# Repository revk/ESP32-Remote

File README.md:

# ESP32-Remote

Now at [Codeberg](https://codeberg.org/RevK/ESP32-Remote)

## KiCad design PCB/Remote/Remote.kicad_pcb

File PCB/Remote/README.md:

# Remote

## Trademark

This project is subject to the licence in the LICENCE file, and even if that says it is an open source project, you cannot sell boards or cases bearing the Andrews & Arnold Ltd name, the A&A logo, the registered trademark AJK logo or other registered trademarks, or any GS1 allocated EANs/barcode assigned to Andrews & Arnold Ltd.

## PCB Designs

These files are for use with [KiCAD](https://www.kicad.org).

- [Remote](Remote.kicad_pro)

## 3D

3D case designs are normally automatically created from the PCB so as to ensure correct details and placement of apertures, etc.

- [blankplate](blankplate.stl)
- [Knob](Knob.stl)
- [Remote------](Remote------.stl)
- [Remote-----B](Remote-----B.stl)
- [Remote----I-](Remote----I-.stl)
- [Remote----IB](Remote----IB.stl)
- [Remote---C--](Remote---C--.stl)
- [Remote---C-B](Remote---C-B.stl)
- [Remote---CI-](Remote---CI-.stl)
- [Remote---CIB](Remote---CIB.stl)
- [Remote--D---](Remote--D---.stl)
- [Remote--D--B](Remote--D--B.stl)
- [Remote--D-I-](Remote--D-I-.stl)
- [Remote--D-IB](Remote--D-IB.stl)
- [Remote--DC--](Remote--DC--.stl)
- [Remote--DC-B](Remote--DC-B.stl)
- [Remote--DCI-](Remote--DCI-.stl)
- [Remote--DCIB](Remote--DCIB.stl)
- [Remote-Base](Remote-Base.stl)
- [Remote-P----](Remote-P----.stl)
- [Remote-P---B](Remote-P---B.stl)
- [Remote-P--I-](Remote-P--I-.stl)
- [Remote-P--IB](Remote-P--IB.stl)
- [Remote-P-C--](Remote-P-C--.stl)
- [Remote-P-C-B](Remote-P-C-B.stl)
- [Remote-P-CI-](Remote-P-CI-.stl)
- [Remote-P-CIB](Remote-P-CIB.stl)
- [Remote-PD---](Remote-PD---.stl)
- [Remote-PD--B](Remote-PD--B.stl)
- [Remote-PD-I-](Remote-PD-I-.stl)
- [Remote-PD-IB](Remote-PD-IB.stl)
- [Remote-PDC--](Remote-PDC--.stl)
- [Remote-PDC-B](Remote-PDC-B.stl)
- [Remote-PDCI-](Remote-PDCI-.stl)
- [Remote-PDCIB](Remote-PDCIB.stl)

## PCB Images

---

*Auto generated README.md 2026-01-03T10:27:57*

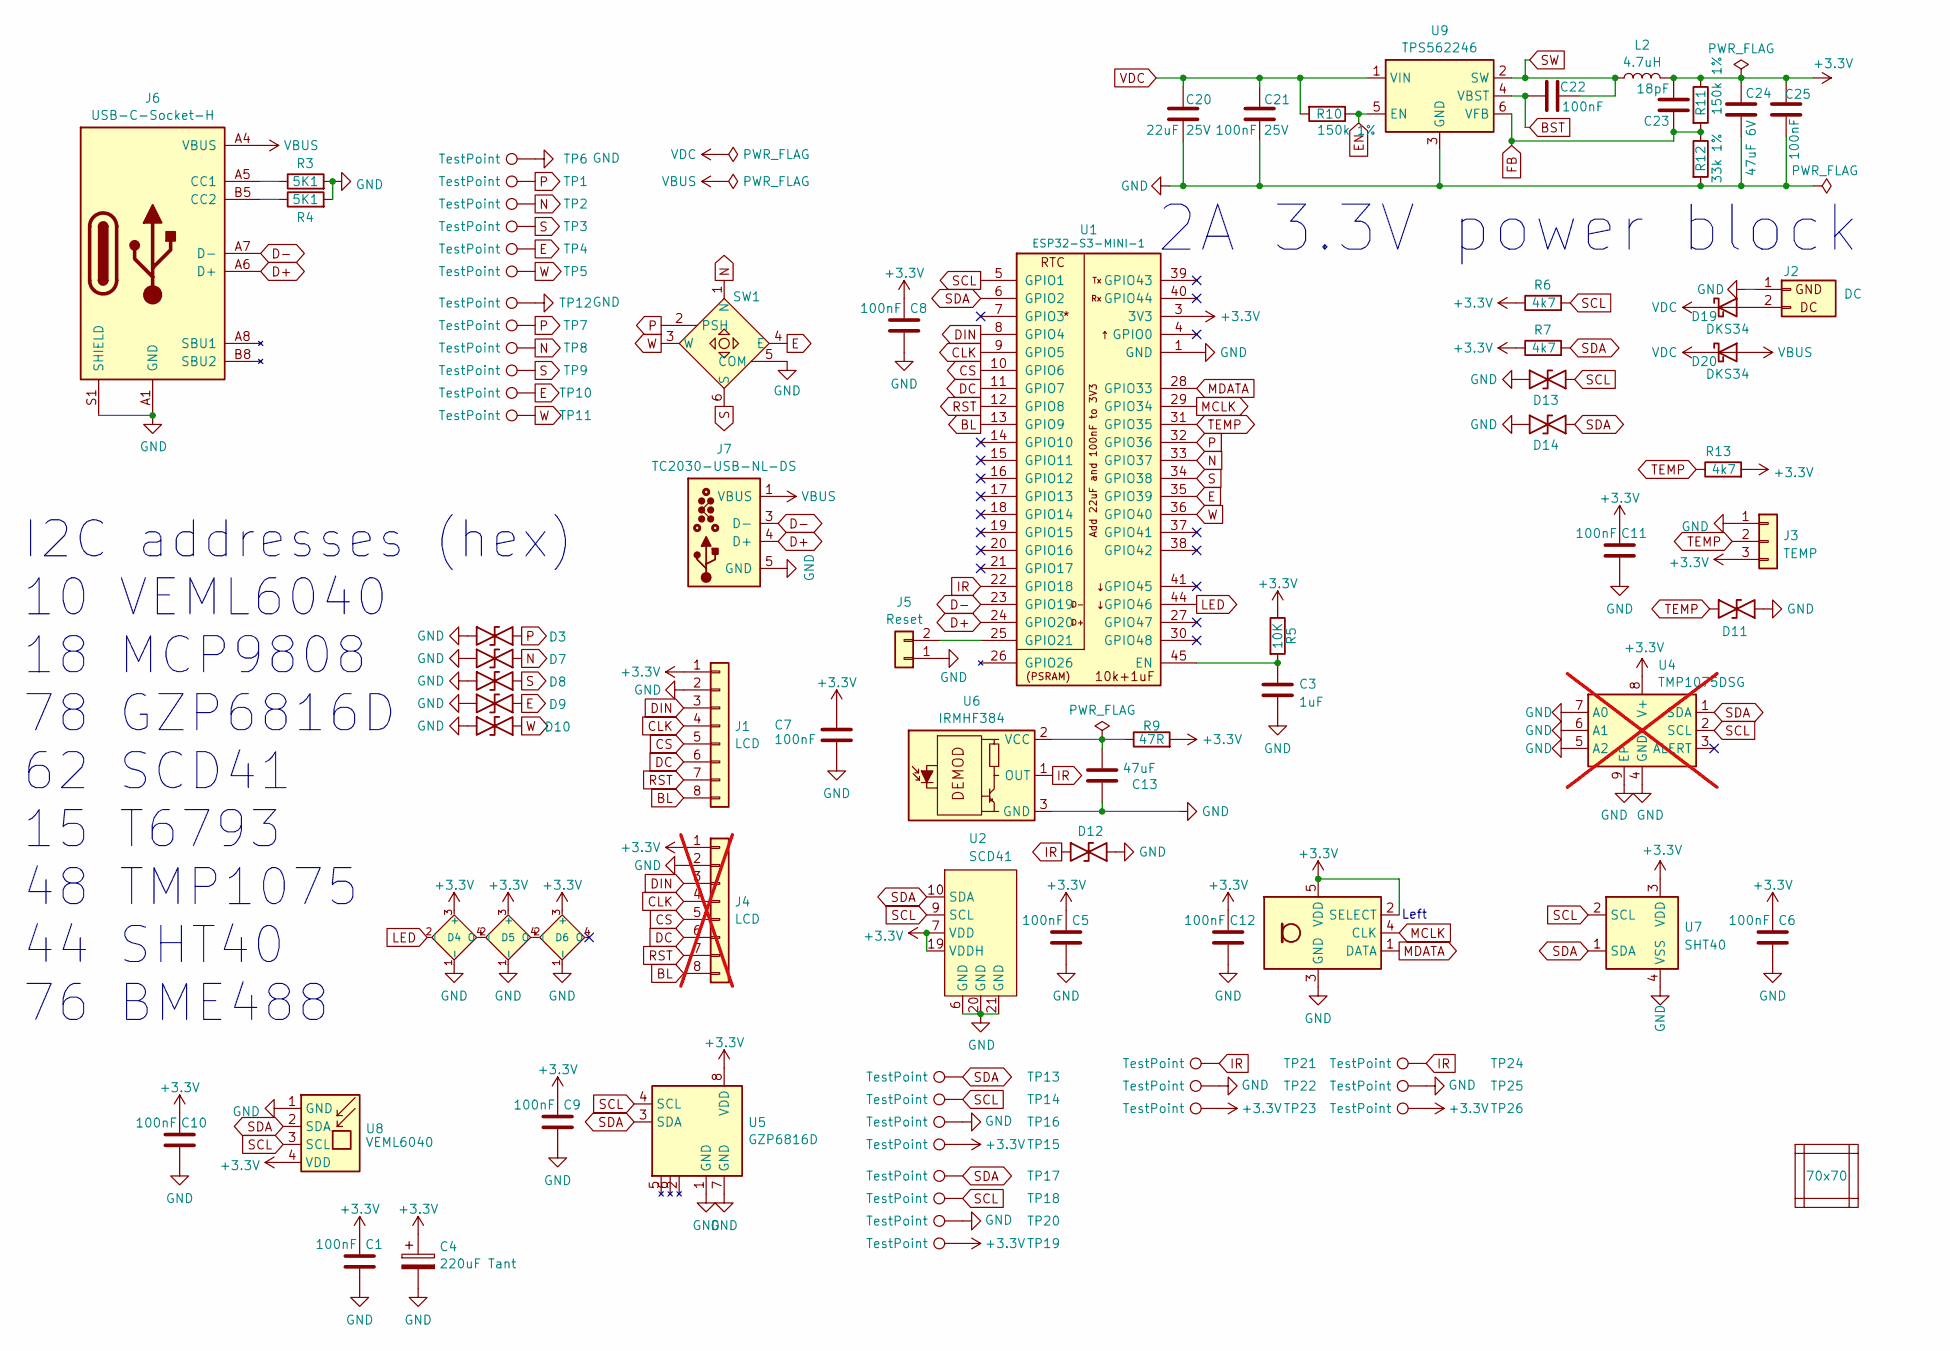
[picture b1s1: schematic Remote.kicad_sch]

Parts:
C1, C5, C6, C8, C9, C10, C11, C12, C22, C25: 100nF; C_0201; MPN C76934
C3: 1uF; C_0201
C4: 220uF Tant; CP_EIA-3528-21_Kemet-B; MPN C122649
C7: 100nF; C_0201
C13: 47uF; C_0603
C20: 22uF 25V; C_0805; MPN C45783
C21: 100nF 25V; C_0402; MPN C56392
C23: 18pF; C_0201; MPN C62164
C24: 47uF 6V; C_0805; MPN C16780
D3, D7, D8, D9, D10, D11, D12, D13, D14: DFN1006-2L; MPN C5137770
D4: XL-1615RGBC-2812B; SMD1615-Side; MPN C5349954
D5, D6: XL-1010RGBC-WS2812B; SMD1615-Side; MPN C5349954
D19, D20: DKS34; D_SOD-123FL; MPN C727076
J1: LCD; LCD2; MPN C42380985
J2: DC; WAGO-2060-452-998-404; MPN C2765055
J3: TEMP; WAGO-2060-453-998-404; MPN C2765056
J4: LCD; PinHeader_1x08_P2.54mm_Vertical; MPN C42380985; not fitted
J5: Reset; AA-Pad
J6: USB-C-Socket-H; MPN C709357
J7: TC2030-USB-NL-DS; Tag-Connect_TC2030-IDC-NL_2x03_P1.27mm_Vertical
L2: 4.7uH; L_5x5; MPN C307876
PCB1: 70x70; PCB7070
R3, R4: 5K1; R_0201; MPN C473460
R5: 10K; R_0201; MPN C102690
R6, R7, R13: 4k7; R_0201; MPN C7467262
R9: 47R; R_0402; MPN C854484
R10, R11: 150k 1%; R_0201; MPN C310173
R12: 33k 1%; R_0201; MPN C320835
SW1: Switch-Nav5; MPN C145900
T1: T3902_MEMS_Mic; T3902_MEMS_Mic_Open; MPN C3171752
TP1, TP2, TP3, TP4, TP5, TP7, TP8, TP9, TP10, TP11, TP13, TP14, TP15, TP17, TP18, TP19, TP21, TP23, TP24, TP26: TestPoint; TestPad
TP6, TP12, TP16, TP20, TP22, TP25: TestPoint; TestPadSquare
U1: ESP32-S3-MINI-1; MPN C3013941
U2: SCD41; MPN C3659294
U4: TMP1075DSG; WSON-8-1EP_2x2mm_P0.5mm_EP0.9x1.6mm_ThermalVias-Side; MPN C2870250; not fitted
U5: GZP6816D; Bosch_LGA-8_2x2.5mm_P0.65mm_ClockwisePinNumbering; MPN C3038127
U6: IRMHF384; IR-SMD-4P,3.35x3.9mm; MPN C7280961
U7: SHT40; Sensirion_DFN-4_1.5x1.5mm_P0.5mm_SHT4x-Side; MPN C2909890
U8: VEML6040; VEML6040-Side; MPN C78465
U9: TPS562246; SOT-5x3-6; MPN C41833479
V1, V2, V3, V4: VCUT70

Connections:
+3.3V: C1.2, C4.1, C5.2, C6.2, C7.1, C8.2, C9.2, C10.2, C11.2, C12.2, C23.2, C24.1, C25.2, D4.3 (+), D5.3 (+), D6.3 (+), J1.1, J3.3, J4.1, L2.2, R5.1, R6.1, R7.1, R9.2, R11.1, R13.2, T1.2 (SELECT), T1.5 (VDD), TP15.1, TP19.1, TP23.1, TP26.1, U1.3 (3V3), U2.7 (VDD), U2.19 (VDDH), U5.8 (VDD), U7.3 (VDD), U8.4 (VDD)
BL: J1.8, J4.8, U1.13 (GPIO9)
BST: C22.1, U9.4 (VBST)
CLK: J1.4, J4.4, U1.9 (GPIO5)
CS: J1.5, J4.5, U1.10 (GPIO6)
D+: J6.A6 (D+), J6.B6 (D+), J7.4 (D+), U1.24 (GPIO20)
D-: J6.A7 (D-), J6.B7 (D-), J7.2 (NC), J7.3 (D-), J7.6 (NC), U1.23 (GPIO19)
DC: J1.6, J4.6, U1.11 (GPIO7)
DIN: J1.3, J4.3, U1.8 (GPIO4)
E: D9.1, SW1.4 (E), TP4.1, TP10.1, U1.35 (GPIO39)
EN: R10.1, U9.5 (EN)
FB: C23.1, R11.2, R12.1, U9.6 (VFB)
GND: C1.1, C3.2, C4.2, C5.1, C6.1, C7.2, C8.1, C9.1, C10.1, C11.1, C12.1, C13.2, C20.2, C21.2, C24.2, C25.1, D3.2, D4.1 (-), D5.1 (-), D6.1 (-), D7.2, D8.2, D9.2, D10.2, D11.1, D12.1, D13.1, D14.1, J1.2, J2.1 (GND), J3.1, J4.2, J5.1, J6.A1 (GND), J6.A12 (GND), J6.B1 (GND), J6.B12 (GND), J6.S1 (SHIELD), J7.5 (GND), R3.2, R4.2, R12.2, SW1.5 (COM), T1.3 (GND), TP6.1, TP12.1, TP16.1, TP20.1, TP22.1, TP25.1, U1.1 (GND), U1.2 (GND), U1.42 (GND), U1.43 (GND), U1.46 (GND), U1.47 (GND), U1.48 (GND), U1.49 (GND), U1.50 (GND), U1.51 (GND), U1.52 (GND), U1.53 (GND), U1.54 (GND), U1.55 (GND), U1.56 (GND), U1.57 (GND), U1.58 (GND), U1.59 (GND), U1.60 (GND), U1.61 (GND), U1.62 (GND), U1.63 (GND), U1.64 (GND), U1.65 (GND), U2.6 (GND), U2.20 (GND), U2.21 (GND), U5.1 (GND), U5.7 (GND), U6.3 (GND), U6.4 (GND), U7.4 (VSS), U8.1 (GND), U9.3 (GND)
IR: D12.2, TP21.1, TP24.1, U1.22 (GPIO18), U6.1 (OUT)
LED: D4.2 (I), U1.44 (GPIO46)
MCLK: T1.4 (CLK), U1.29 (GPIO34)
MDATA: T1.1 (DATA), U1.28 (GPIO33)
N: D7.1, SW1.1 (N), TP2.1, TP8.1, U1.33 (GPIO37)
unnamed: D4.4 (O), D5.2 (I)
unnamed: D5.4 (O), D6.2 (I)
unnamed: D19.2 (A), J2.2 (DC)
unnamed: J5.2, U1.25 (GPIO21)
unnamed: J6.A5 (CC1), R3.1
unnamed: J6.B5 (CC2), R4.1
unnamed: C3.1, R5.2, U1.45 (EN)
unnamed: C13.1, R9.1, U6.2 (VCC)
P: D3.1, SW1.2 (PSH), TP1.1, TP7.1, U1.32 (GPIO36)
RST: J1.7, J4.7, U1.12 (GPIO8)
S: D8.1, SW1.6 (S), TP3.1, TP9.1, U1.34 (GPIO38)
SCL: D13.2, R6.2, TP14.1, TP18.1, U1.5 (GPIO1), U2.5 (DNC), U2.9 (SCL), U4.2 (SCL), U5.4 (SCL), U7.2 (SCL), U8.3 (SCL)
SDA: D14.2, R7.2, TP13.1, TP17.1, U1.6 (GPIO2), U2.10 (SDA), U5.3 (SDA), U7.1 (SDA), U8.2 (SDA)
SW: C22.2, L2.1, U9.2 (SW)
TEMP: D11.2, J3.2, R13.1, U1.31 (GPIO35)
VBUS: D20.2 (A), J6.A4 (VBUS), J6.A9 (VBUS), J6.B4 (VBUS), J6.B9 (VBUS), J7.1 (VBUS)
VDC: C20.1, C21.1, D19.1 (K), D20.1 (K), R10.2, U9.1 (VIN)
W: D10.1, SW1.3 (W), TP5.1, TP11.1, U1.36 (GPIO40)

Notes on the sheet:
2A 3.3V power block
I2C addresses (hex) 10 VEML6040 18 MCP9808 78 GZP6816D 62 SCD41 15 T6793 48 TMP1075 44 SHT40 76 BME488
Left

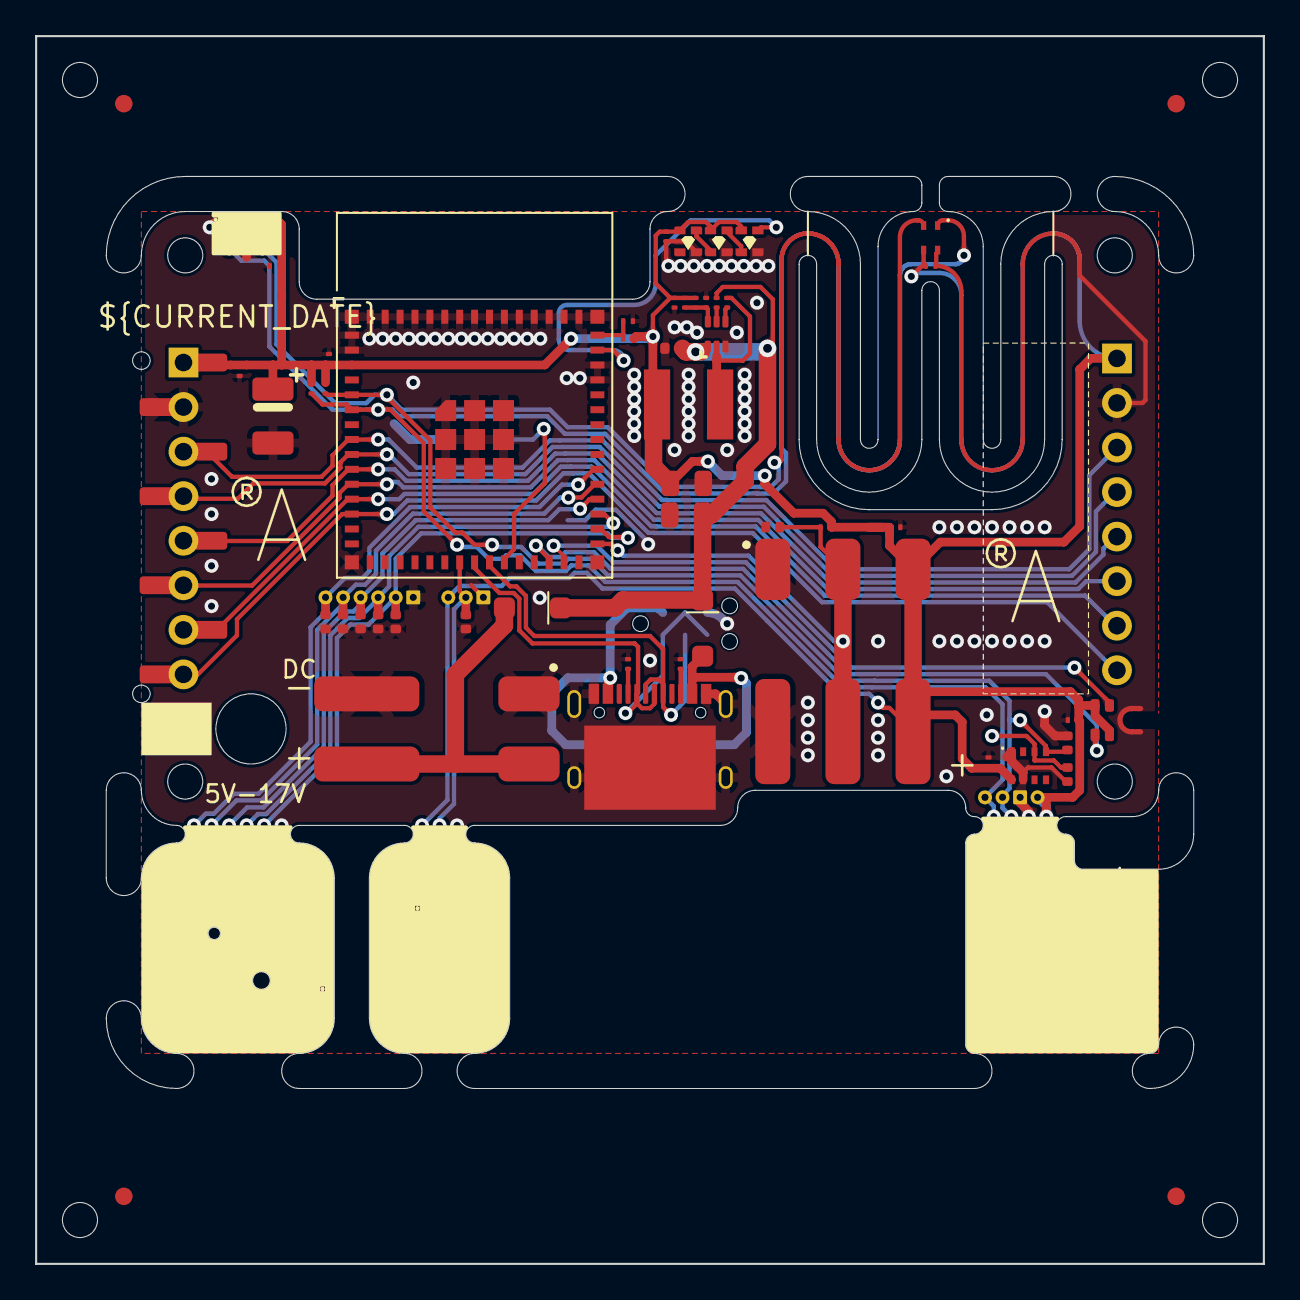
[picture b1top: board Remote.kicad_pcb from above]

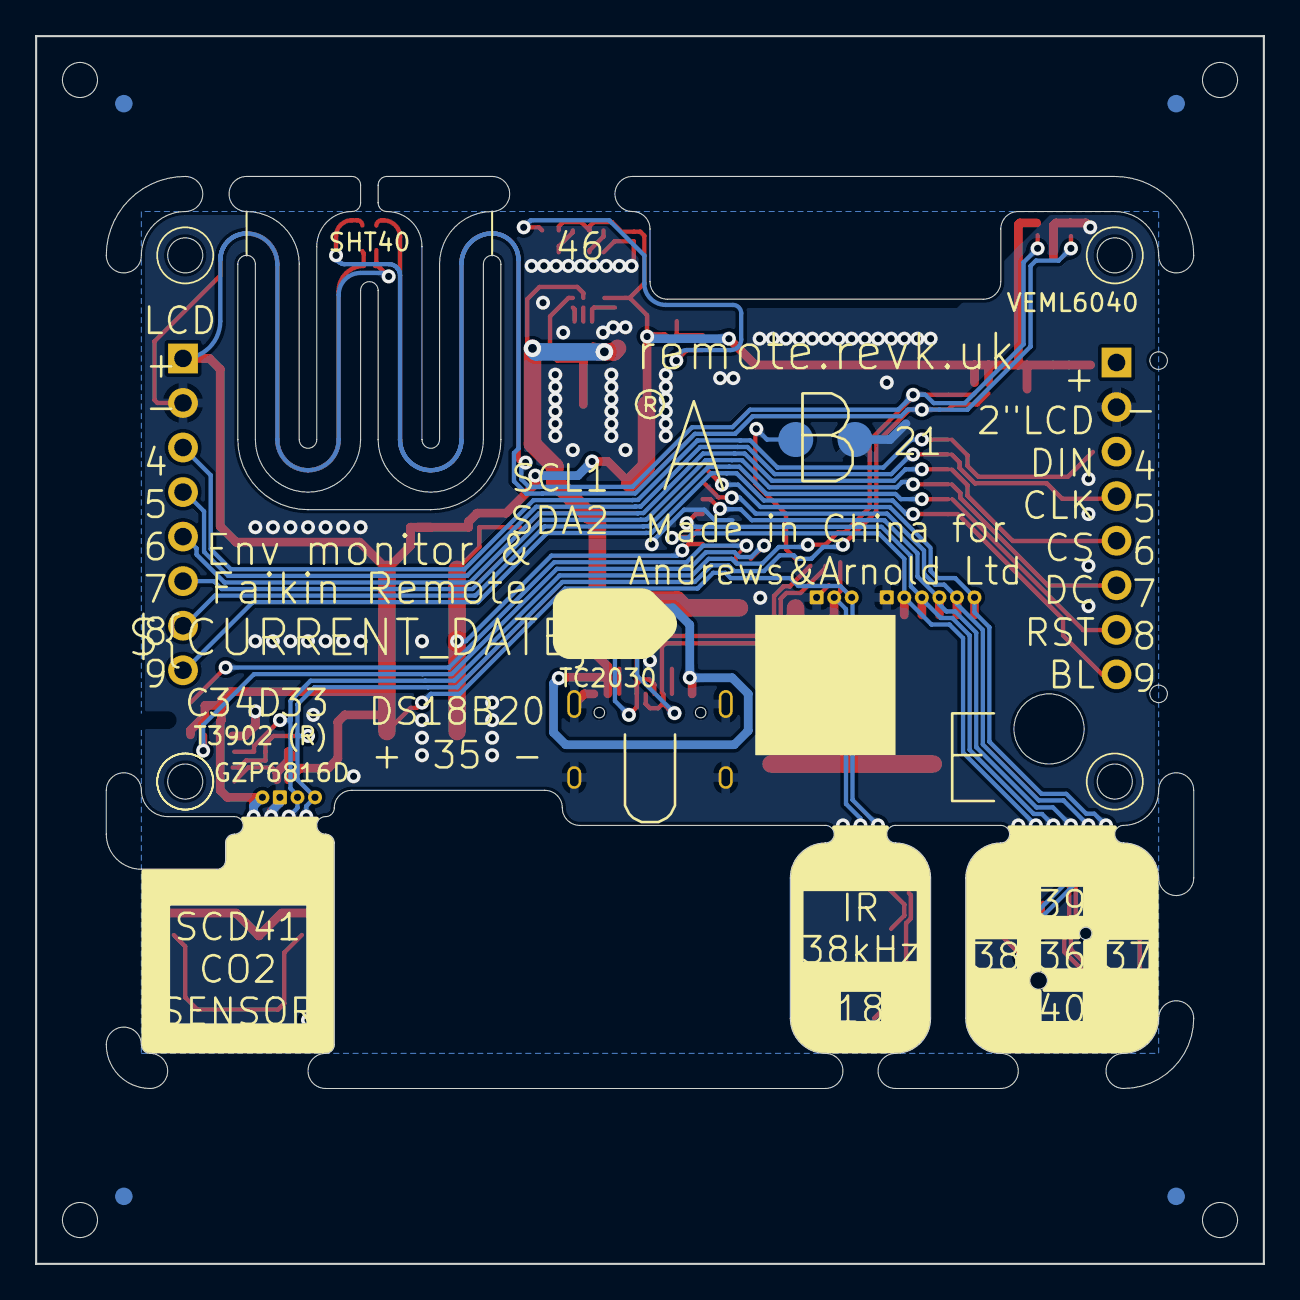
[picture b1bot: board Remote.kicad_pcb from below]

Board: 2 copper layers, 70.0 x 70.0 mm, 90 parts (3 on the bottom side), 36 nets.

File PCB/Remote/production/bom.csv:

Designator,Footprint,Quantity,Value,LCSC Part #
"C1, C10, C11, C12, C22, C25, C5, C6, C8, C9",C_0201,10,100nF,C76934
C13,C_0603,1,47uF,
C20,C_0805,1,22uF 25V,C45783
C21,C_0402,1,100nF 25V,C56392
C23,C_0201,1,18pF,C62164
C24,C_0805,1,47uF 6V,C16780
C3,C_0201,1,1uF,
C4,CP_EIA-3528-21_Kemet-B,1,220uF Tant,C122649
C7,C_0201,1,100nF,
"D10, D11, D12, D13, D14, D3, D7, D8, D9",DFN1006-2L,9,~,C5137770
"D19, D20",D_SOD-123FL,2,DKS34,C727076
D4,SMD1615-Side,1,XL-1615RGBC-2812B,C5349954
"D5, D6",SMD1615-Side,2,XL-1010RGBC-WS2812B,C5349954
J1,LCD2,1,LCD,C42380985
J2,WAGO-2060-452-998-404,1,DC,C2765055
J3,WAGO-2060-453-998-404,1,TEMP,C2765056
J6,USB-C-Socket-H,1,USB-C-Socket-H,C709357
L2,L_5x5,1,4.7uH,C307876
"R10, R11",R_0201,2,150k 1%,C310173
R12,R_0201,1,33k 1%,C320835
"R13, R6, R7",R_0201,3,4k7,C7467262
"R3, R4",R_0201,2,5K1,C473460
R5,R_0201,1,10K,C102690
R9,R_0402,1,47R,C854484
SW1,Switch-Nav5,1,~,C145900
T1,T3902_MEMS_Mic_Open,1,T3902_MEMS_Mic,C3171752
U1,ESP32-S3-MINI-1,1,ESP32-S3-MINI-1,C3013941
U2,SCD41,1,SCD41,C3659294
U5,Bosch_LGA-8_2x2.5mm_P0.65mm_ClockwisePinNumbering,1,GZP6816D,C3038127
U6,"IR-SMD-4P,3.35x3.9mm",1,IRMHF384,C7280961
U7,Sensirion_DFN-4_1.5x1.5mm_P0.5mm_SHT4x-Side,1,SHT40,C2909890
U8,VEML6040-Side,1,VEML6040,C78465
U9,SOT-5x3-6,1,TPS562246,C41833479

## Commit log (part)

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2025-05-05 tweak
2025-05-05 Tidy icons for Rh and CO2
2025-05-05 Beta
2025-05-05 Consistent spacing
2025-05-05 FFS again
2025-05-05 Release
2025-05-06 New btn and temp reporting
2025-05-06 New button working mode
2025-05-06 New button logic - 4 way not 5
2025-05-06 Library update
2025-05-06 Tidy
2025-05-06 D'Oh
2025-05-06 RH 2 places
2025-05-06 RH BLE fix
2025-05-07 Avoid radiator fighting cooling
2025-05-07 scd41to
2025-05-07 RH delay too
2025-05-08 Many tweaks including SCD41 temp offset
2025-05-08 Auocal
2025-05-08 Timed darkness
2025-05-08 autocal
2025-05-08 Reporting
2025-05-08 /status
2025-05-08 Rework
2025-05-08 Updated design
2025-05-09 Started on new casework
2025-05-10 Change to SHT so humidity when no CO2
2025-05-10 Cases
2025-05-10 Adjust radiator logic
2025-05-10 atest renders
2025-05-10 case
2025-05-10 rad on until close
2025-05-10 0 rh fix
2025-05-10 Tweak rad
2025-05-10 Latest render
2025-05-10 Tidy no mode
2025-05-10 TGweak
2025-05-11 Radiator control logic taken from old envmon code.
2025-05-11 Rad timer fix
2025-05-11 Help
2025-05-11 SCD41 start time
2025-05-11 no.faikin
2025-05-11 Tweaks
2025-05-11 Target and target revert
2025-05-12 FFS messed up timer logic
2025-05-12 Tidy case design
2025-05-12 CO2 if CO2 found
2025-05-12 More LEDs
2025-05-12 Revert step
2025-05-13 Latest renders and tweaks
2025-05-13 BLE MAC Match
2025-05-14 Mic added
2025-05-14 Updated icons
2025-05-14 icon tidy
2025-05-15 Tidy SCD startup
2025-05-15 SCD41 startup, and tweak landscape
2025-05-15 Tweak layout of screen
2025-05-15 Icons
2025-05-15 Icon
2025-05-15 bulk
2025-05-15 VEML seems unreliable, oddly
2025-05-16 low/high display levels
2025-05-17 memory usage
2025-05-20 Reworked for connecting switch/SCD41
2025-05-21 New rendere
2025-05-21 Tidy rendering
2025-05-21 Clean up BOM
2025-05-22 Chasing memory leak
2025-05-22 Nice reboot screen
2025-05-22 rhsmall
2025-05-22 General EPD
2025-05-23 Black
2025-05-25 Better clearance on USB lead
2025-05-26 Default fan
2025-05-26 Cosmetic
2025-05-27 BL and hold
2025-05-27 Invalid DS18B20 temp
2025-05-29 Tidy# Please enter the commit message for your changes. Lines starting
2025-05-29 SHT40
2025-05-29 RH select
2025-05-30 TV remotes
2025-05-30 Generic/TV IR
2025-05-30 Clean up keys and repeat logic on IR
2025-05-30 IR remote
2025-05-30 Fine tuning
2025-05-30 bright fix
2025-05-30 TODo
2025-05-31 IR# with '#' will be ignored, and an empty message aborts the commit.
2025-05-31 Noise
2025-05-31 HA noise fix
2025-05-31 Re render/case
2025-05-31 COmment
2025-05-31 Moved around
2025-06-02 Case update
2025-06-02 Case improvement - but needs more work
2025-06-02 Much tidy
2025-06-03 Cleaner fade
2025-06-03 New layout - IR back to sensible place
2025-06-07 Moved mic
2025-06-12 More cases
2025-07-05 handle -inf, etc
2025-07-06 temp unit
2025-07-09 Latest renders
2025-07-14 wider
2025-07-14 New tracks for temp
2025-07-17 Update reg
2025-07-26 MPNs
2025-07-26 Clearing inductror
2025-07-28 Defaults
2025-08-09 Fix merge
2025-08-09 Render
2025-08-09 New renders and case
2025-08-11 New render
2025-08-12 Re-render
2025-08-13 v-cut
2025-08-13 Bottoms
2025-08-13 Fix BOM/pos
2025-08-14 Re render and new knob
2025-08-15 LED controls for triple LED boards
2025-08-15 Blank
2025-08-16 new case
2025-08-17 Cleaner casework
2025-08-18 A *lot* of case options
2025-08-18 Case fix (base)
2025-08-22 dark setting green LEDs off
2025-08-26 README and new render
2025-09-10 Changed temp sense selection and allowing 3xDS18B20
2025-10-10 New LED
2025-11-15 Lib update
2025-11-15 Started name change
2025-11-15 Name change
2025-11-15 Update dependancies
2025-11-15 DS18B20m update
2025-11-15 Tidy (new name)
2026-01-02 Tweaks, but cases look wrong
2026-01-02 Still buggered
2026-01-03 Improved case design
2026-01-05 New LED lib
2026-01-08 Manifest
2026-01-08 Build files
2026-02-03 Fan control fix
2026-02-13 submodule
2026-02-15 Codeberg
